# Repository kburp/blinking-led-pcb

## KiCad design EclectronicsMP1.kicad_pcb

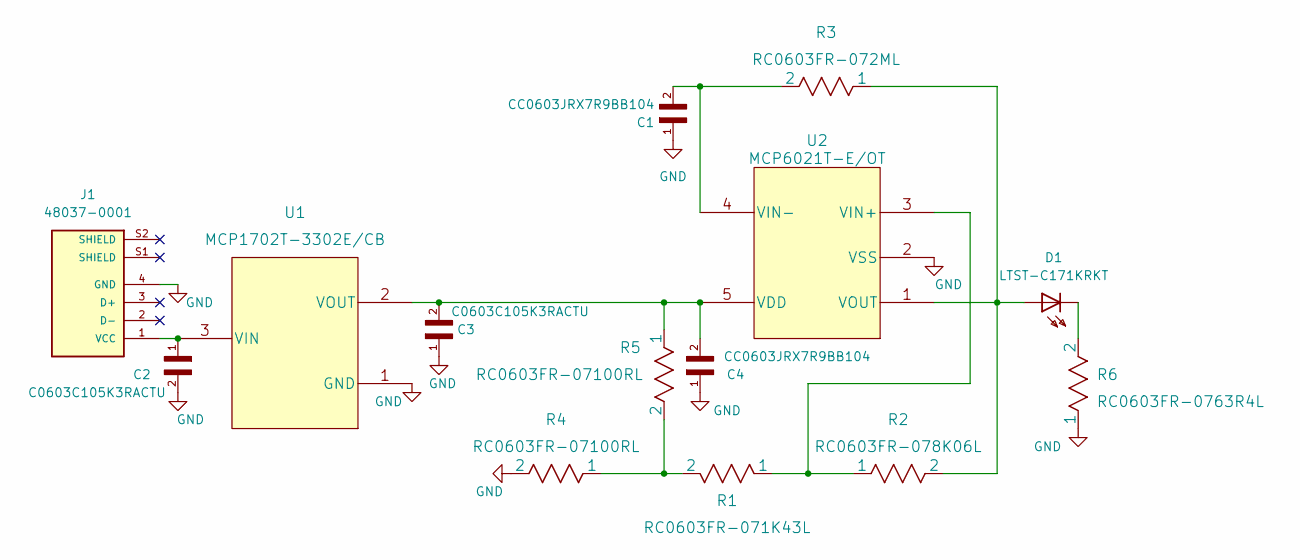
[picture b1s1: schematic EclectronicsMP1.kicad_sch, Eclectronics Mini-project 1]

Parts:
C1, C4: CC0603JRX7R9BB104; CAPC1608X90
C2, C3: C0603C105K3RACTU; CAPC1608X90
D1: LTST-C171KRKT; DIOC200X125X110
J1: 48037-0001; MOLEX_48037-0001; PARTREV D
R1: RC0603FR-071K43L
R2: RC0603FR-078K06L
R3: RC0603FR-072ML
R4, R5: RC0603FR-07100RL
R6: RC0603FR-0763R4L
U1: MCP1702T-3302E/CB; MCP1702T-3302E&slash_CB
U2: MCP6021T-E/OT; MCP6021T-E&slash_OT

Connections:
GND: C1.1, C2.2, C3.1, C4.1, J1.4 (GND), R4.2, R6.1, U1.1 (GND), U2.2 (VSS)
unnamed: C1.2, R3.2, U2.4 (VIN-)
unnamed: C2.1, J1.1 (VCC), U1.3 (VIN)
unnamed: C3.2, C4.2, R5.1, U1.2 (VOUT), U2.5 (VDD)
unnamed: D1.+, R2.2, R3.1, U2.1 (VOUT)
unnamed: D1.-, R6.2
unnamed: R1.1, R2.1, U2.3 (VIN+)
unnamed: R1.2, R4.1, R5.2

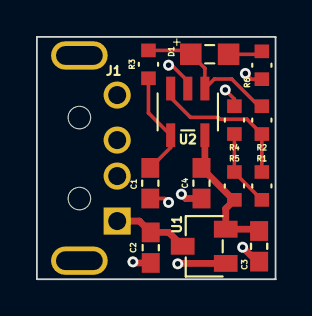
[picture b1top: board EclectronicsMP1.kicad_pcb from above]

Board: 2 copper layers, 13.3 x 13.5 mm, 14 parts (0 on the bottom side), 8 nets.

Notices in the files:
parts and their libraries:
Copyright 2021 Accelerated Designs. All rights reserved.
